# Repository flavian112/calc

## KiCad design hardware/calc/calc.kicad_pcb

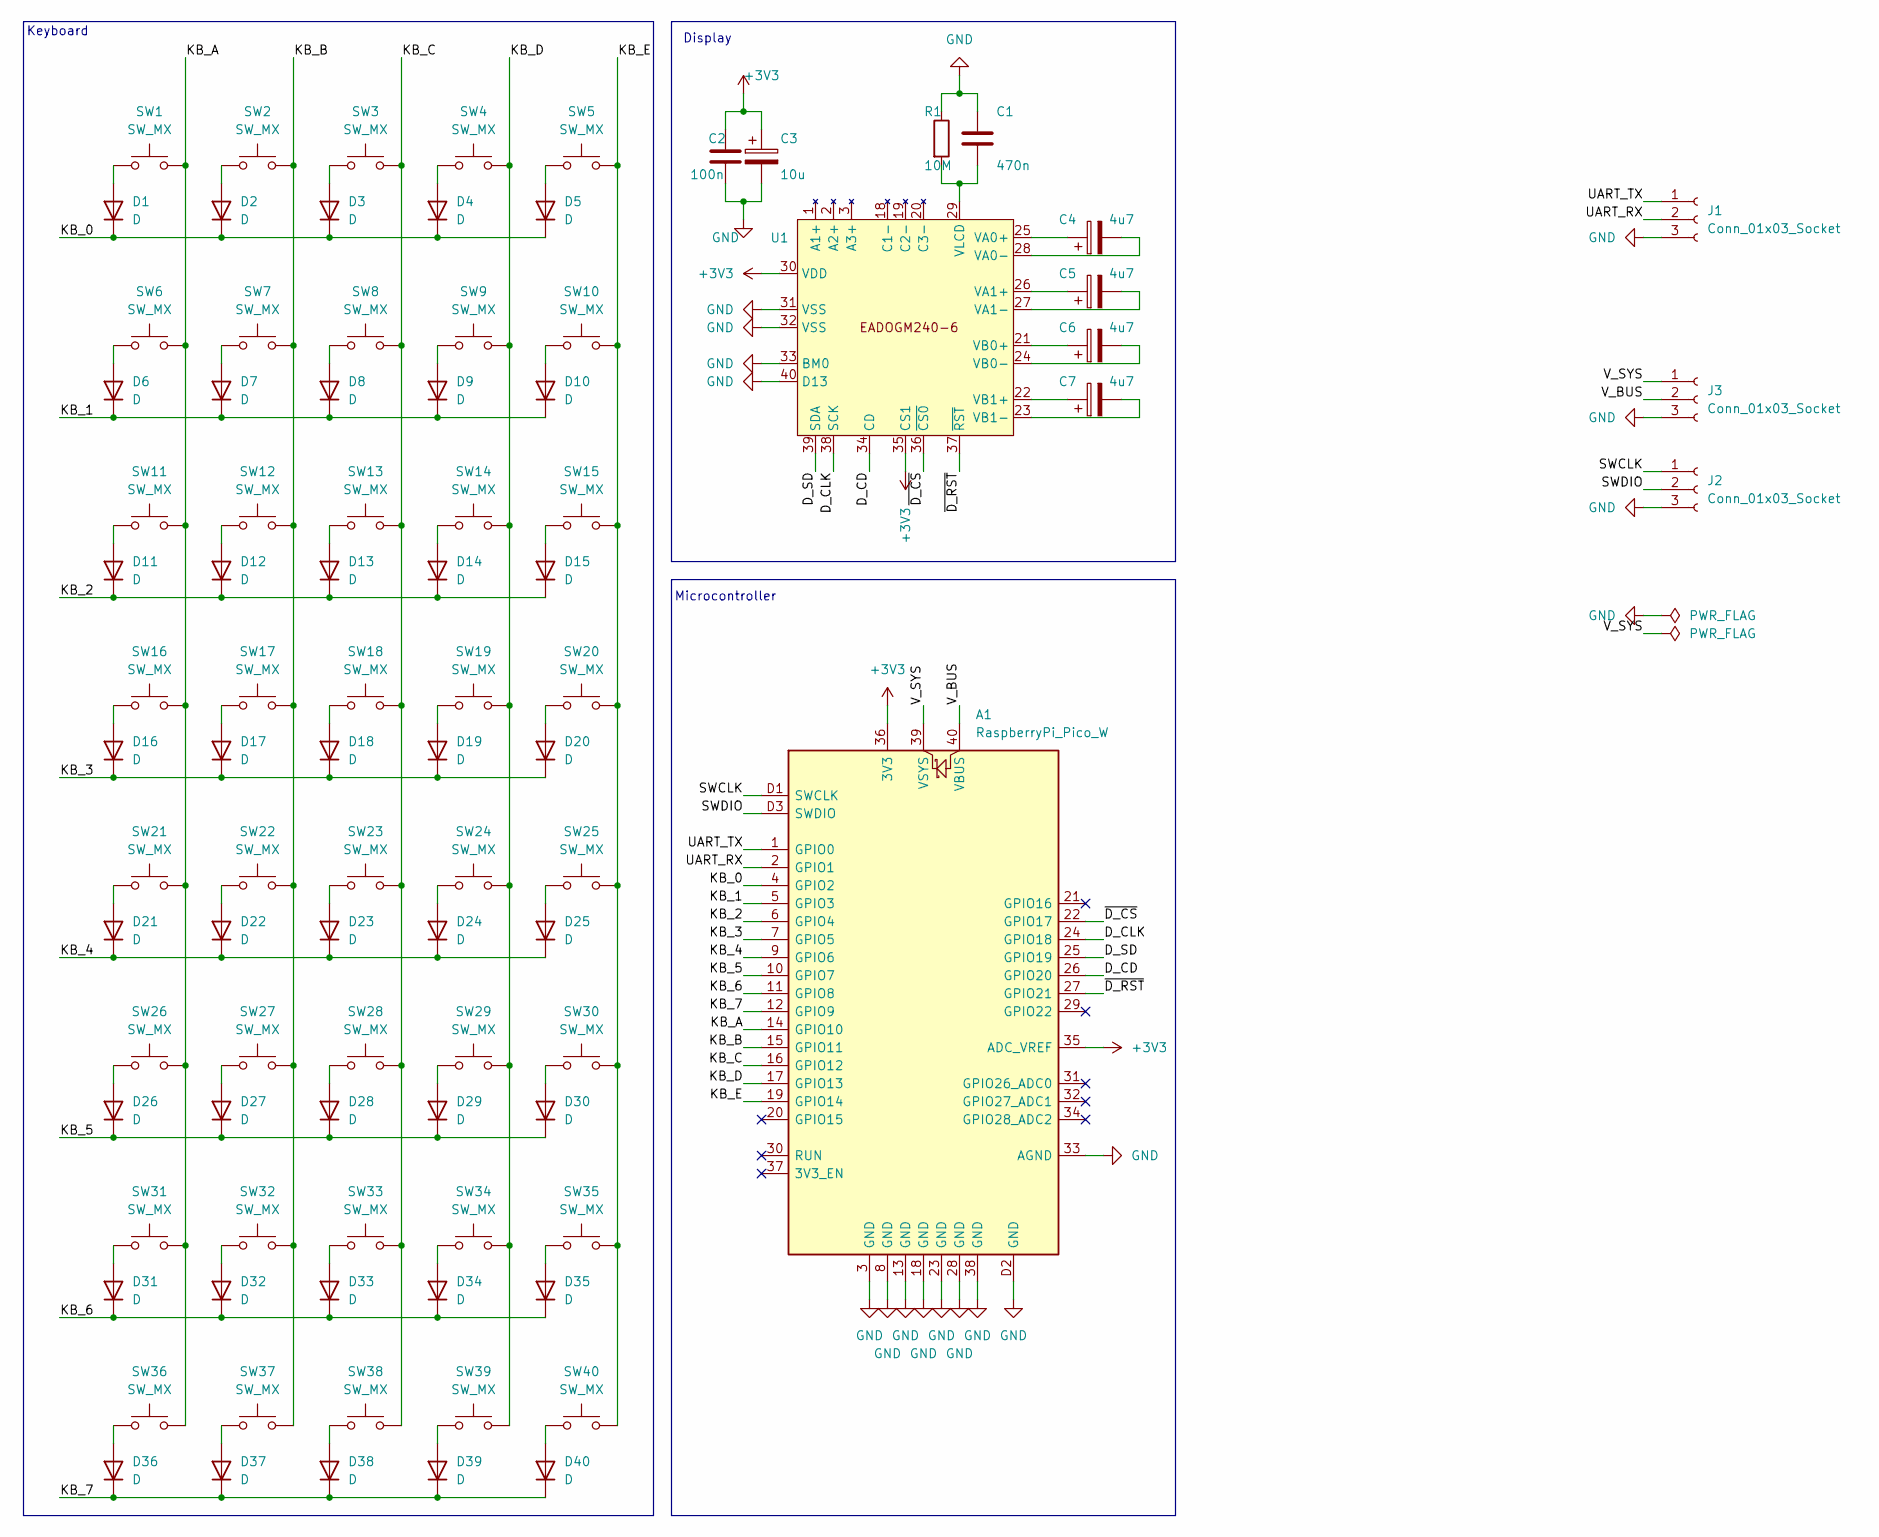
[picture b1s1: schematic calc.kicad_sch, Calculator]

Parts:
A1: RaspberryPi_Pico_W; RaspberryPi_Pico
C1: 470n; C_Rect_L4.0mm_W2.5mm_P2.50mm
C2: 100n; C_Rect_L4.0mm_W2.5mm_P2.50mm
C3: 10u; CP_Radial_D5.0mm_P2.50mm
C4, C5, C6, C7: 4u7; CP_Radial_D5.0mm_P2.50mm
D1, D2, D3, D4, D5, D6, D7, D8, D9, D10, D11, D12, D13, D14, D15, D16, D17, D18, D19, D20, D21, D22, D23, D24, D25, D26, D27, D28, D29, D30, D31, D32, D33, D34, D35, D36, D37, D38, D39, D40: D; D_DO-41_SOD81_P7.62mm_Horizontal
J1, J2, J3: Conn_01x03_Socket; PinSocket_1x03_P2.54mm_Horizontal
R1: 10M; R_Axial_DIN0207_L6.3mm_D2.5mm_P7.62mm_Horizontal
SW1, SW2, SW3, SW4, SW5, SW6, SW7, SW8, SW9, SW10, SW11, SW12, SW13, SW14, SW15, SW16, SW17, SW18, SW19, SW20, SW21, SW22, SW23, SW24, SW25, SW26, SW27, SW28, SW29, SW30, SW31, SW32, SW33, SW34, SW35, SW36, SW37, SW38, SW39, SW40: SW_MX; MX2A-E1NW
U1: EADOGM240-7

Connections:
+3V3: A1.35 (ADC_VREF), A1.36 (3V3), C2.1, C3.1, U1.30 (VDD), U1.35 (CS1)
/D_CD: A1.26 (GPIO20), U1.34 (CD)
/D_CLK: A1.24 (GPIO18), U1.38 (SCK)
/D_SD: A1.25 (GPIO19), U1.39 (SDA)
/KB_0: A1.4 (GPIO2), D1.1 (K), D2.1 (K), D3.1 (K), D4.1 (K), D5.1 (K)
/KB_1: A1.5 (GPIO3), D6.1 (K), D7.1 (K), D8.1 (K), D9.1 (K), D10.1 (K)
/KB_2: A1.6 (GPIO4), D11.1 (K), D12.1 (K), D13.1 (K), D14.1 (K), D15.1 (K)
/KB_3: A1.7 (GPIO5), D16.1 (K), D17.1 (K), D18.1 (K), D19.1 (K), D20.1 (K)
/KB_4: A1.9 (GPIO6), D21.1 (K), D22.1 (K), D23.1 (K), D24.1 (K), D25.1 (K)
/KB_5: A1.10 (GPIO7), D26.1 (K), D27.1 (K), D28.1 (K), D29.1 (K), D30.1 (K)
/KB_6: A1.11 (GPIO8), D31.1 (K), D32.1 (K), D33.1 (K), D34.1 (K), D35.1 (K)
/KB_7: A1.12 (GPIO9), D36.1 (K), D37.1 (K), D38.1 (K), D39.1 (K), D40.1 (K)
/KB_A: A1.14 (GPIO10), SW1.2, SW6.2, SW11.2, SW16.2, SW21.2, SW26.2, SW31.2, SW36.2
/KB_B: A1.15 (GPIO11), SW2.2, SW7.2, SW12.2, SW17.2, SW22.2, SW27.2, SW32.2, SW37.2
/KB_C: A1.16 (GPIO12), SW3.2, SW8.2, SW13.2, SW18.2, SW23.2, SW28.2, SW33.2, SW38.2
/KB_D: A1.17 (GPIO13), SW4.2, SW9.2, SW14.2, SW19.2, SW24.2, SW29.2, SW34.2, SW39.2
/KB_E: A1.19 (GPIO14), SW5.2, SW10.2, SW15.2, SW20.2, SW25.2, SW30.2, SW35.2, SW40.2
/SWCLK: A1.D1 (SWCLK), J2.1
/SWDIO: A1.D3 (SWDIO), J2.2
/UART_RX: A1.2 (GPIO1), J1.2
/UART_TX: A1.1 (GPIO0), J1.1
/V_BUS: A1.40 (VBUS), J3.2
/V_SYS: A1.39 (VSYS), J3.1
/~D_CS: A1.22 (GPIO17), U1.36 (~CS0)
/~D_RST: A1.27 (GPIO21), U1.37 (~RST)
GND: A1.3 (GND), A1.8 (GND), A1.13 (GND), A1.18 (GND), A1.23 (GND), A1.28 (GND), A1.33 (AGND), A1.38 (GND), A1.D2 (GND), C1.1, C2.2, C3.2, J1.3, J2.3, J3.3, R1.1, U1.31 (VSS), U1.32 (VSS), U1.33 (BM0), U1.40 (D13)
unnamed: D1.2 (A), SW1.1
unnamed: D2.2 (A), SW2.1
unnamed: D3.2 (A), SW3.1
unnamed: D4.2 (A), SW4.1
unnamed: D5.2 (A), SW5.1
unnamed: D6.2 (A), SW6.1
unnamed: D7.2 (A), SW7.1
unnamed: D8.2 (A), SW8.1
unnamed: D9.2 (A), SW9.1
unnamed: D10.2 (A), SW10.1
unnamed: D11.2 (A), SW11.1
unnamed: D12.2 (A), SW12.1
unnamed: D13.2 (A), SW13.1
unnamed: D14.2 (A), SW14.1
unnamed: D15.2 (A), SW15.1
unnamed: D16.2 (A), SW16.1
unnamed: D17.2 (A), SW17.1
unnamed: D18.2 (A), SW18.1
unnamed: D19.2 (A), SW19.1
unnamed: D20.2 (A), SW20.1
unnamed: D21.2 (A), SW21.1
unnamed: D22.2 (A), SW22.1
unnamed: D23.2 (A), SW23.1
unnamed: D24.2 (A), SW24.1
unnamed: D25.2 (A), SW25.1
unnamed: D26.2 (A), SW26.1
unnamed: D27.2 (A), SW27.1
unnamed: D28.2 (A), SW28.1
unnamed: D29.2 (A), SW29.1
unnamed: D30.2 (A), SW30.1
unnamed: D31.2 (A), SW31.1
unnamed: D32.2 (A), SW32.1
unnamed: D33.2 (A), SW33.1
unnamed: D34.2 (A), SW34.1
unnamed: D35.2 (A), SW35.1
unnamed: D36.2 (A), SW36.1
unnamed: D37.2 (A), SW37.1
unnamed: D38.2 (A), SW38.1
unnamed: D39.2 (A), SW39.1
unnamed: D40.2 (A), SW40.1
unnamed: C4.1, U1.25 (VA0+)
unnamed: C4.2, U1.28 (VA0-)
unnamed: C5.1, U1.26 (VA1+)
unnamed: C5.2, U1.27 (VA1-)
unnamed: C6.1, U1.21 (VB0+)
unnamed: C6.2, U1.24 (VB0-)
unnamed: C7.1, U1.22 (VB1+)
unnamed: C7.2, U1.23 (VB1-)
unnamed: C1.2, R1.2, U1.29 (VLCD)

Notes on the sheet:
Microcontroller
Display
Keyboard

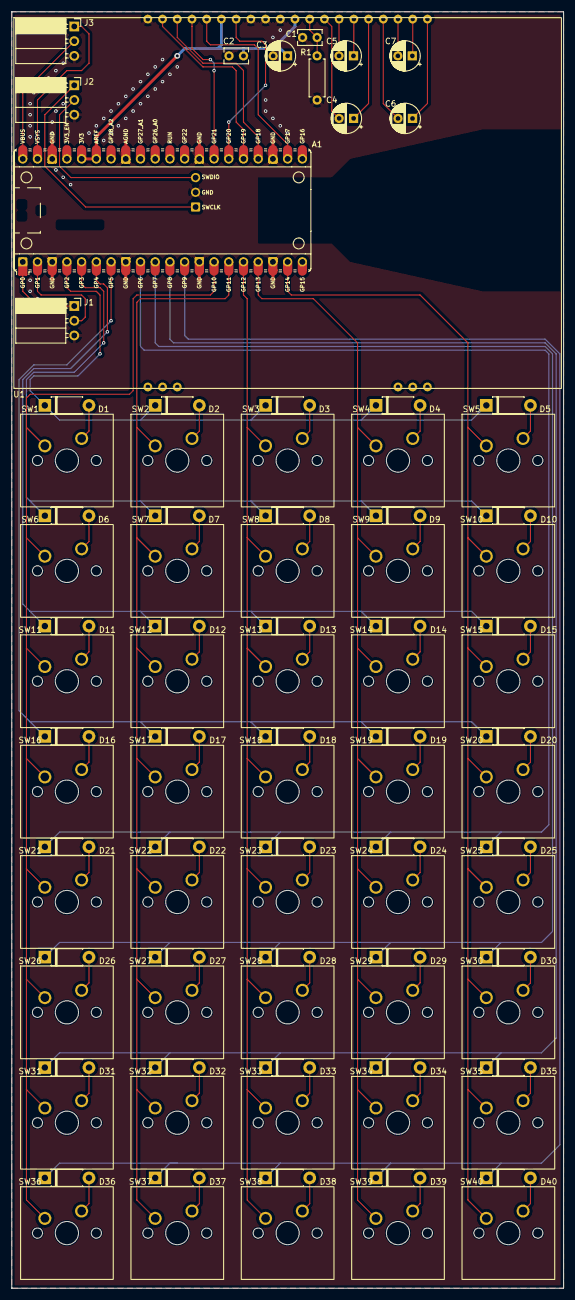
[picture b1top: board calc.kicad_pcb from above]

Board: 2 copper layers, 95.2 x 220.3 mm, 93 parts (0 on the bottom side), 75 nets.

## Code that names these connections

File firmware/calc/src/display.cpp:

#include "display.h"

#include <Arduino.h>
#include <SPI.h>
#include <U8g2lib.h>

#define PIN_D_SCK  (18)
#define PIN_D_MOSI (19)
#define PIN_D_CS   (17)
#define PIN_D_CD   (20)
#define PIN_D_RST  (21)

static U8G2_UC1611_EA_DOGXL240_F_4W_SW_SPI u8g2(U8G2_R2, 
                                                PIN_D_SCK,
                                                PIN_D_MOSI, 
                                                PIN_D_CS, 
                                                PIN_D_CD, 
                                                PIN_D_RST);

static uint8_t disp_w;
static uint8_t disp_h;

void dp_init(void) {
    u8g2.begin();
    u8g2.clearDisplay();
    disp_w = u8g2.getDisplayWidth();
    disp_h = u8g2.getDisplayHeight();
}

void dp_clear_buf() {
  u8g2.clearBuffer();
}

void dp_send_buf() {
  u8g2.sendBuffer();
}


void dp_draw_menu(const char labels[5][6]) {
  uint8_t box_h = 11;
  uint8_t box_w = (disp_w / 5) - 2;
  uint8_t box_y = disp_h - box_h;
 
  u8g2.setFont(u8g2_font_profont15_mr);
  u8g2.setFontMode(true);
  for (int i = 0; i < 5; ++i) {
    uint8_t box_x = (i * (disp_w / 5)) + 1;
    
    u8g2.setDrawColor(1);
    u8g2.drawBox(box_x, box_y, box_w, box_h);
    u8g2.setDrawColor(0);
    u8g2.drawGlyph(box_x + 4, disp_h - 1, labels[i][0]);
    u8g2.drawGlyph(box_x + 12, disp_h - 1, labels[i][1]);
    u8g2.drawGlyph(box_x + 20, disp_h - 1, labels[i][2]);
    u8g2.drawGlyph(box_x + 28, disp_h - 1, labels[i][3]);
    u8g2.drawGlyph(box_x + 36, disp_h - 1, labels[i][4]);

  }
}

void dp_draw_text(const char *text, uint8_t row) {
  u8g2.setFont(u8g2_font_profont29_mr);
  u8g2.setDrawColor(1);
  u8g2.drawStr(0, disp_h - 15 - (row * 23), text);
}

void dp_draw_flags(bool sl, bool sr, bool alt, bool alph, bool hyp, bool nav) {
  u8g2.setDrawColor(1);
  u8g2.drawBox(0, 0, disp_w, 11);
  u8g2.setDrawColor(0);

  if (sl) {
    u8g2.drawLine(2, 6, 8, 6);
    u8g2.drawLine(8, 6, 8, 2);
    u8g2.drawLine(2, 6, 5, 4);
    u8g2.drawLine(2, 6, 5, 8);
  }

  if (sr) {
    u8g2.drawLine(11 + 8, 6, 11 + 2, 6);
    u8g2.drawLine(11 + 2, 6, 11 + 2, 2);
    u8g2.drawLine(11 + 8, 6, 11 + 5, 4);
    u8g2.drawLine(11 + 8, 6, 11 + 5, 8);
  }

  if (alt) {
    u8g2.drawLine(22 + 2, 3, 22 + 3, 3);
    u8g2.drawLine(22 + 6, 3, 22 + 8, 3);
    u8g2.drawLine(22 + 3, 3, 22 + 6, 7);
    u8g2.drawLine(22 + 6, 7, 22 + 8, 7);
  }

  if (alph) {
    u8g2.drawLine(33 + 2, 8, 33 + 4, 8);
    u8g2.drawLine(33 + 6, 8, 33 + 8, 8);
    u8g2.drawLine(33 + 3, 8, 33 + 5, 2);
    u8g2.drawLine(33 + 7, 8, 33 + 5, 2);
    u8g2.drawLine(33 + 3, 6, 33 + 7, 6);
  }

  if (hyp) {
    u8g2.drawLine(44 + 3, 2, 44 + 3, 8);
    u8g2.drawLine(44 + 7, 2, 44 + 7, 8);
    u8g2.drawLine(44 + 3, 5, 44 + 7, 5);
  }

}

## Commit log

2024-11-28 initial
2024-11-29 multicore
2024-11-29 input formatter
2024-12-07 refactor
2024-12-27 mod keys
2025-01-04 constants
